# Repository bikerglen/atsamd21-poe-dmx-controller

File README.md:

# atsamd21-poe-dmx-controller
This project is a DMX controller that generates RGB light patterns. It has a browser-based user interface for controlling the patterns.

Two hardware platforms are supported:

For quick prototyping, the hardware can be built using a Particle Ethernet Feather Wing, an Adafruit Feather M0 Basic Proto, and the DMX Feather Wing from the boards directory in this repository. These boards all plug together with no additional wiring required.

For more permanent installations, the hardware can be built using a custom board, surface mount components, and a Hammond 1455C801 extruded aluminum enclosure.

The software runs on both platforms without any modifications. The effects.ino file can be modified to add new effects to the controller. The html.ino and style.ino files can be modified to update the user interface.

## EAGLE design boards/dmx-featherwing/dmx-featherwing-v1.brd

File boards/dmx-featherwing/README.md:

The RJ-45 connector is wired using the Color Kinetics pinout. Other lights may require pins 1 and 2 on the RJ-45 to be swapped.

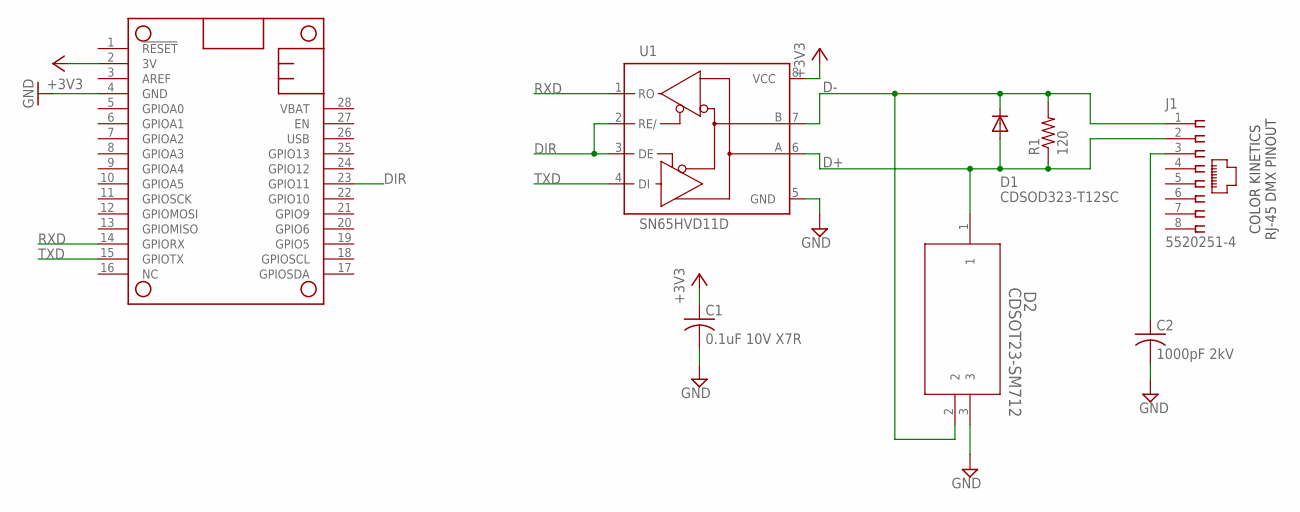
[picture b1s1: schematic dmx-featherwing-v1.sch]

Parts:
C1: 0.1uF 10V X7R; C0805
C2: 1000pF 2kV; C1206K
D1: CDSOD323-T12SC; SOD323-W
D2: CDSOT23-SM712; SOT_SM712
J1: 5520251-4
MS2: FEATHERWING
R1: 120; R0805
U1: SN65HVD11D; SO08

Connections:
+3V3: C1.1, MS2.2 (3V), U1.8 (VCC)
D+: D1.A, D2.1, J1.2, R1.1, U1.6 (A)
D-: D1.C, D2.2, J1.1, R1.2, U1.7 (B)
DIR: MS2.23 (GPIO11), U1.2 (RE/), U1.3 (DE)
GND: C1.2, C2.2, D2.3, MS2.4 (GND), U1.5 (GND)
unnamed: C2.1, J1.3
RXD: MS2.14 (GPIORX), U1.1 (RO)
TXD: MS2.15 (GPIOTX), U1.4 (DI)

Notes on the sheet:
COLOR KINETICS RJ-45 DMX PINOUT

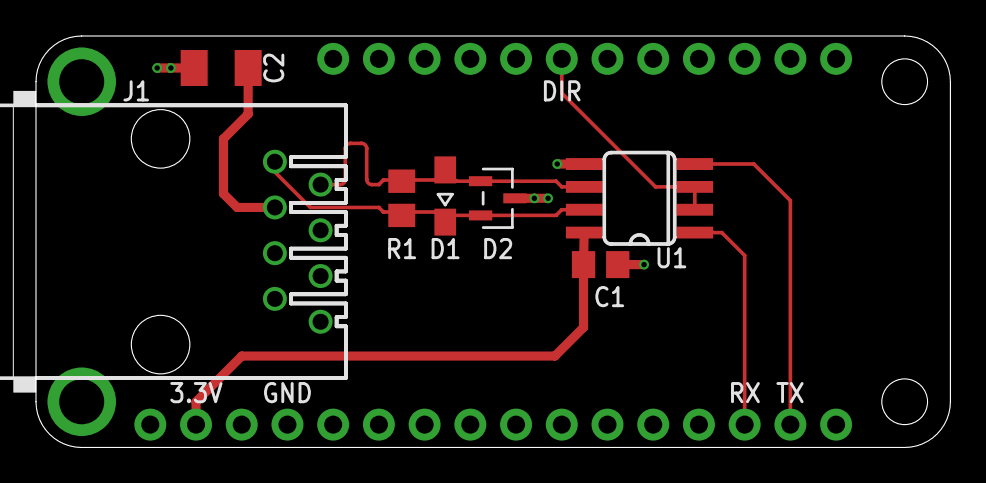
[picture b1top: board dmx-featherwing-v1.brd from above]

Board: 2 copper layers, 50.8 x 22.9 mm, 8 parts (0 on the bottom side), 8 nets.

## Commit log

2020-02-17 initial software checkin
2020-02-17 added dmx featherwing boards
2020-02-17 Added note about connector pinout and fixture compatibility.
2020-02-17 Added termination resistor, ESD protection, and chassis ground.
2020-02-17 Cleaned up DIR trace on PCB.
2020-02-18 add bill of materials
2020-02-18 Fix line breaks in README.md
2020-02-22 fixed R1 name/value, moved DIR label to correct pin
2020-02-28 added code to blink built-in LED inside the effects run loop
2020-02-28 removed debug code which interfered with differential transceiver direction pin
2020-02-28 removed requirement for serial port active, fixed transceiver direction signal, fixed bug when changing modes

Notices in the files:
parts and their libraries:
microbuilder: This work is placed in the public domain, and may be freely used for commercial and non-commercial work with the following conditions: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
